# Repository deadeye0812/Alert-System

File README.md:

This is a alert system, which triggers a buzzer (Piezo Element), by interrupting the laser that points to the phototransistor.

Contained Main Elements:
- Piezo Element
- 555 timer
- Phototransistor
- Comparator
- Battery Cell
- Battery
- BJT

Side Elements:
- 3x10k Resistor
- 2x1uf Capacitor

How it works:

First of all the Battery is responsible for:
- powering the Comparator
- collector current for the Phototransistor in combination with a 10k resistor for a voltage divider for the reference voltage for the comparator
- collector current for the BJT
- a voltage divider for the variable voltage of the comparator
- putting the 555 timer in astable mode

The idea behind it:

Setting the variable voltage of the comparator to a constant value and setting the reference voltage of the comparator to a variable value!!!

Normaly you would use the phototransistor combined in a voltage divider for setting a variable voltage at the comparator.
And you would use the constant voltage divider to create a reference voltage for the comparator.

In this case, the comparator would give us a positive output if the laser shines on the phototransistor.

So my idea was to flip it around!!!

When the laser on the phototransistor now gets interrupted the output of the comparator is positive,
therefore it sends the interruption signal to the BJT which activates the 555 timer in astable mode to trigger a Piezo Element.

Problems:
The alarm works as long as the laser is interrupted, but when it got only short interrupted it instantly stops again.

Future:
Add a second 555 timer in monostable mode to set a period of time in where the alarm goes off.

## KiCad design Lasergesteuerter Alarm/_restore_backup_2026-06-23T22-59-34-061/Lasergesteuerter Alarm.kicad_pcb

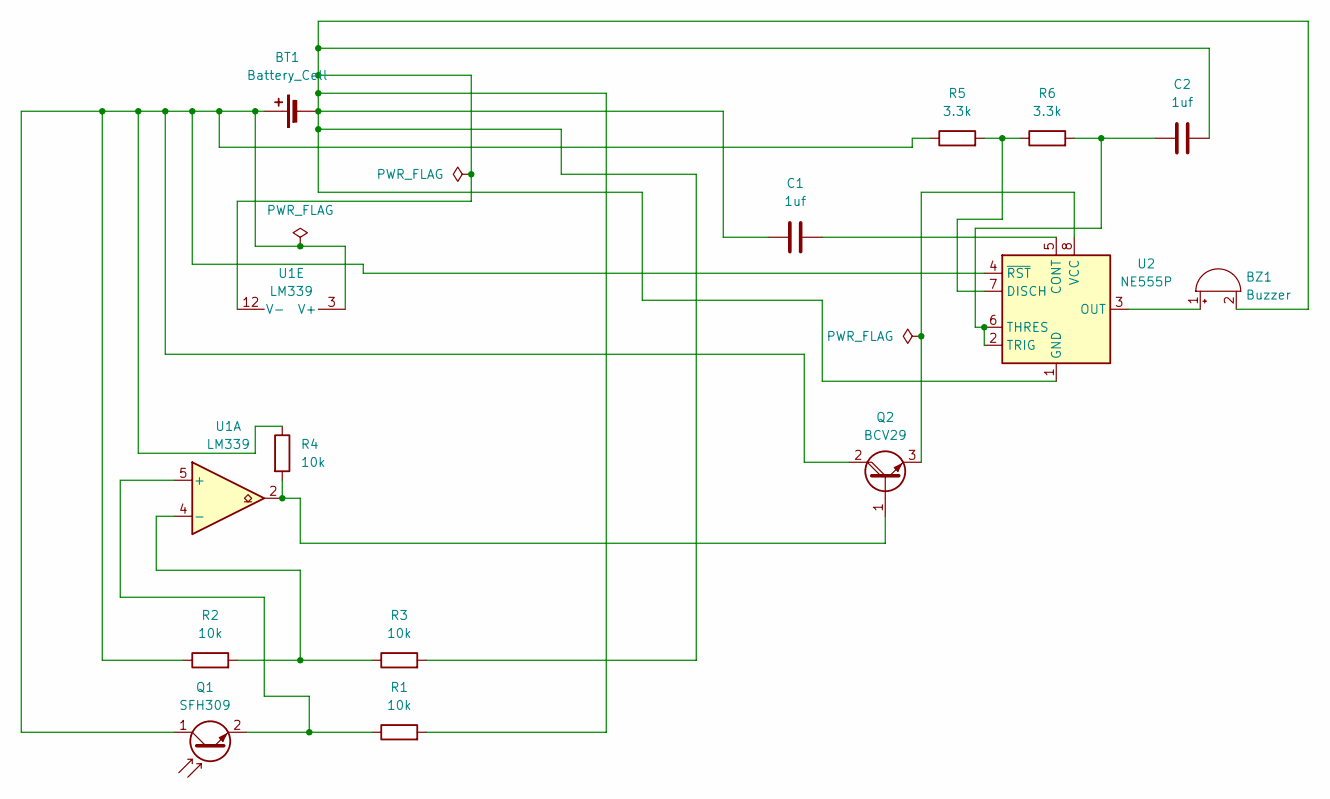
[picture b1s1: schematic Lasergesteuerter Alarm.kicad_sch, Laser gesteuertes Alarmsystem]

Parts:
BT1: Battery_Cell; BatteryHolder_Keystone_2462_2xAA
BZ1: Buzzer; Buzzer_D14mm_H7mm_P10mm
C1: 1uf; CP_Radial_D5.0mm_P2.00mm
C2: 1uf; CP_Radial_D4.0mm_P2.00mm
Q1: SFH309; LED_D3.0mm_Clear
Q2: BCV29; SOT-89-3
R1, R2, R3, R4: 10k; R_Axial_DIN0207_L6.3mm_D2.5mm_P2.54mm_Vertical
R5, R6: 3.3k; R_Axial_DIN0207_L6.3mm_D2.5mm_P2.54mm_Vertical
U1: LM339; SOIC-14W_7.5x9mm_P1.27mm
U2: NE555P; DIP-8_W7.62mm

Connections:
unnamed: BT1.1 (+), Q1.1 (C), Q2.2 (C), R2.1, R4.1, R5.1, U1.3 (V+), U2.4 (~RST)
unnamed: BT1.2 (-), BZ1.2 (-), C1.1, C2.2, R1.2, R3.2, U1.12 (V-), U2.1 (GND)
unnamed: BZ1.1 (+), U2.3 (OUT)
unnamed: Q1.2 (E), R1.1, U1.5 (+)
unnamed: Q2.1 (B), R4.2, U1.2
unnamed: Q2.3 (E), U2.8 (VCC)
unnamed: R2.2, R3.1, U1.4 (-)
unnamed: C1.2, U2.5 (CONT)
unnamed: R5.2, R6.1, U2.7 (DISCH)
unnamed: C2.1, R6.2, U2.2 (TRIG), U2.6 (THRES)

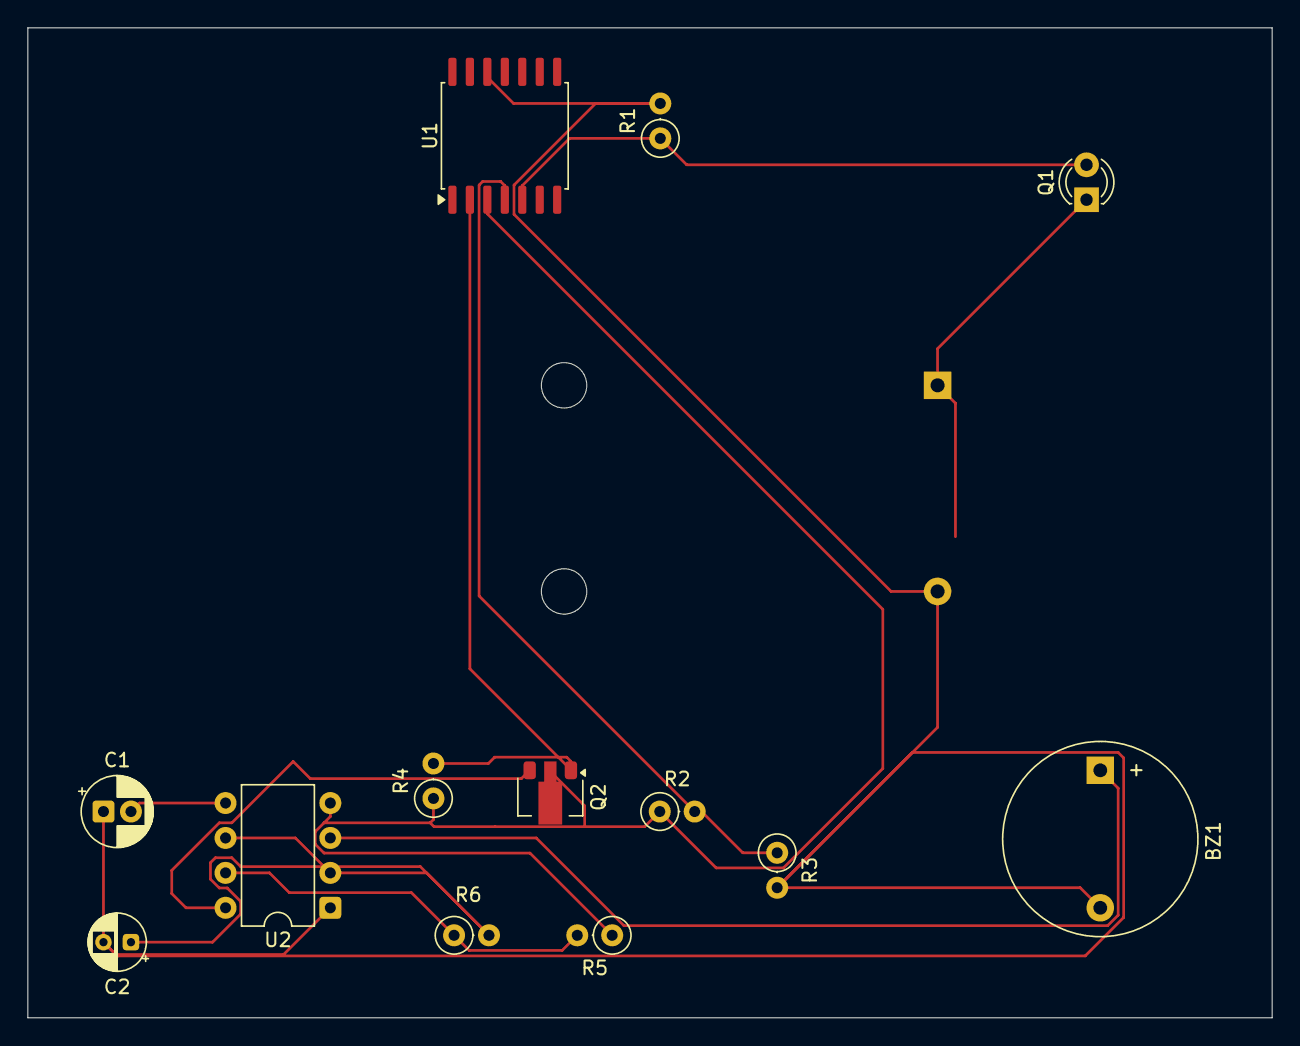
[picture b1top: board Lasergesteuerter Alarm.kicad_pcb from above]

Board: 2 copper layers, 90.5 x 72.0 mm, 14 parts (1 on the bottom side), 10 nets.
